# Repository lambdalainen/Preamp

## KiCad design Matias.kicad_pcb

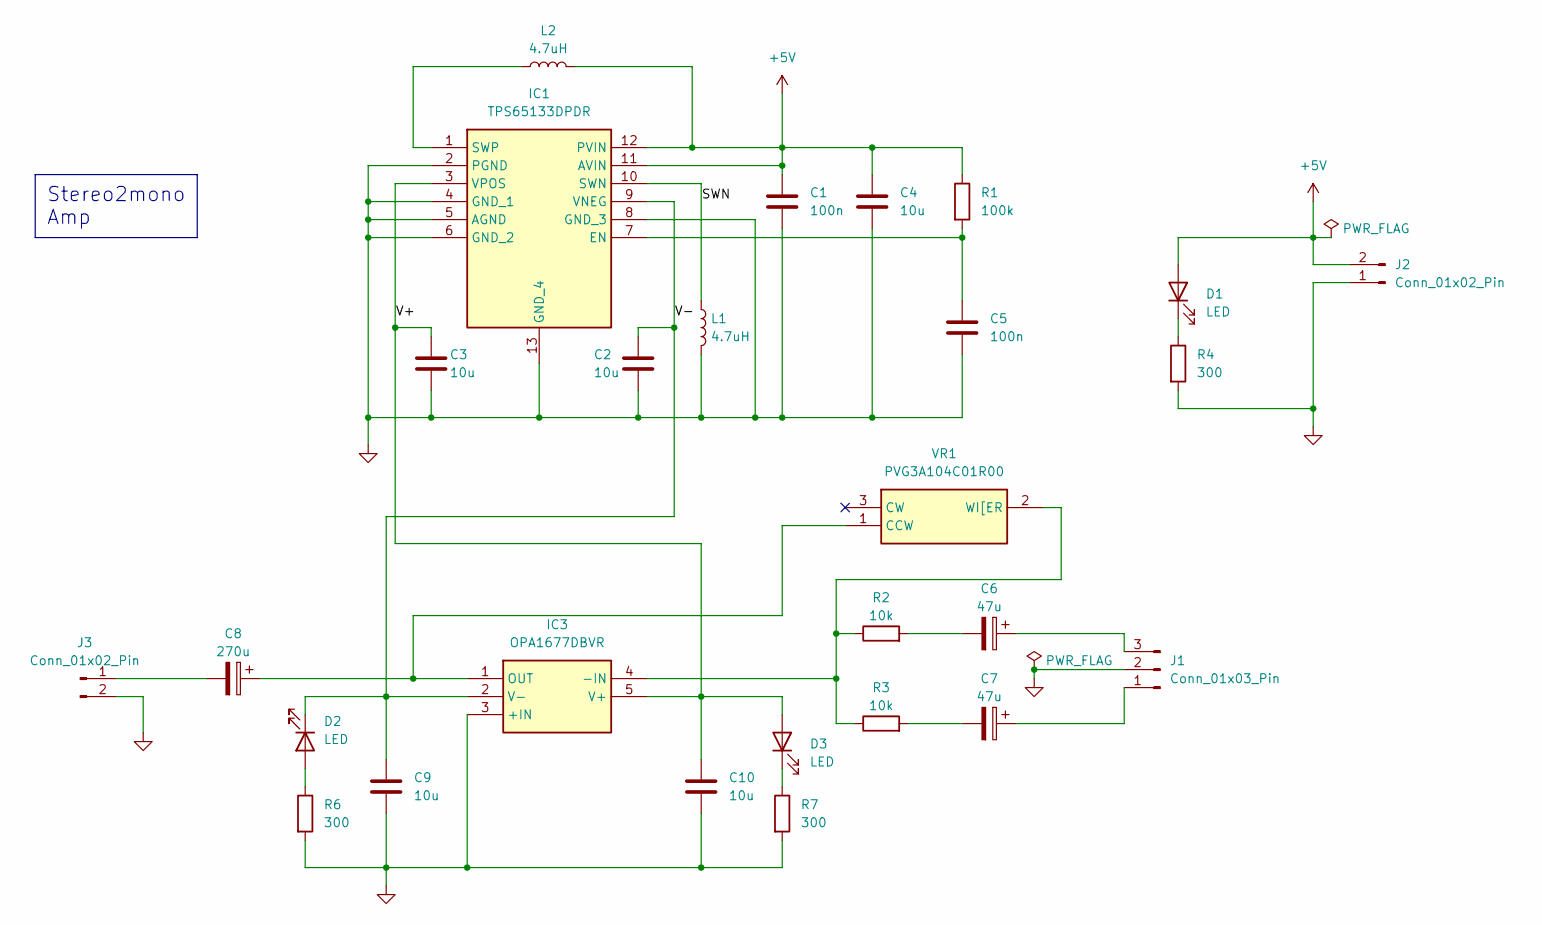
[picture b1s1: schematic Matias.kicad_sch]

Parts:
C1, C5: 100n; C_0603_1608Metric
C2, C3, C4: 10u; C_0805_2012Metric
C6, C7: 47u; CP_Radial_D5.0mm_P2.00mm
C8: 270u; CP_Radial_D6.3mm_P2.50mm
C9, C10: 10u; C_0603_1608Metric
D1, D2, D3: LED; LED_0603_1608Metric
IC1: TPS65133DPDR; SON45P300X300X80-13N-D; Manufacturer_Part_Number TPS65133DPDR; Mouser Part Number 595-TPS65133DPDR
IC3: OPA1677DBVR; SOT95P280X145-5N; Manufacturer_Part_Number OPA1677DBVR; Mouser Part Number 595-OPA1677DBVR
J1: Conn_01x03_Pin; PinHeader_1x03_P2.54mm_Vertical
J2, J3: Conn_01x02_Pin; PinHeader_1x02_P2.54mm_Vertical
L1, L2: 4.7uH; L_1008_2520Metric
R1: 100k; R_0603_1608Metric
R2, R3: 10k; R_0603_1608Metric
R4, R6, R7: 300; R_0603_1608Metric
VR1: PVG3A104C01R00; Manufacturer_Part_Number PVG3A104C01R00; Mouser Part Number 81-PVG3A104C01R00

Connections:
+5V: C1.1, C4.1, D1.2 (A), IC1.11 (AVIN), IC1.12 (PVIN), J2.2, L2.2, R1.1
/SWN: IC1.10 (SWN), L1.1
/V+: C3.1, C10.1, D3.2 (A), IC1.3 (VPOS), IC3.5 (V+)
/V-: C2.1, C9.1, D2.1 (K), IC1.9 (VNEG), IC3.2 (V-)
GND: C1.2, C2.2, C3.2, C4.2, C5.2, C9.2, C10.2, IC1.2 (PGND), IC1.4 (GND_1), IC1.5 (AGND), IC1.6 (GND_2), IC1.8 (GND_3), IC1.13 (GND_4), IC3.3 (+IN), J1.2, J2.1, J3.2, L1.2, R4.2, R6.2, R7.2
unnamed: C6.2, R2.2
unnamed: C7.2, R3.2
unnamed: D1.1 (K), R4.1
unnamed: D2.2 (A), R6.1
unnamed: D3.1 (K), R7.1
unnamed: C5.1, IC1.7 (EN), R1.2
unnamed: IC1.1 (SWP), L2.1
unnamed: IC3.4 (-IN), R2.1, R3.1, VR1.2 (WI[ER)
unnamed: C8.1, IC3.1 (OUT), VR1.1 (CCW)
unnamed: C7.1, J1.1
unnamed: C6.1, J1.3
unnamed: C8.2, J3.1

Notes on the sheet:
Stereo2mono Amp

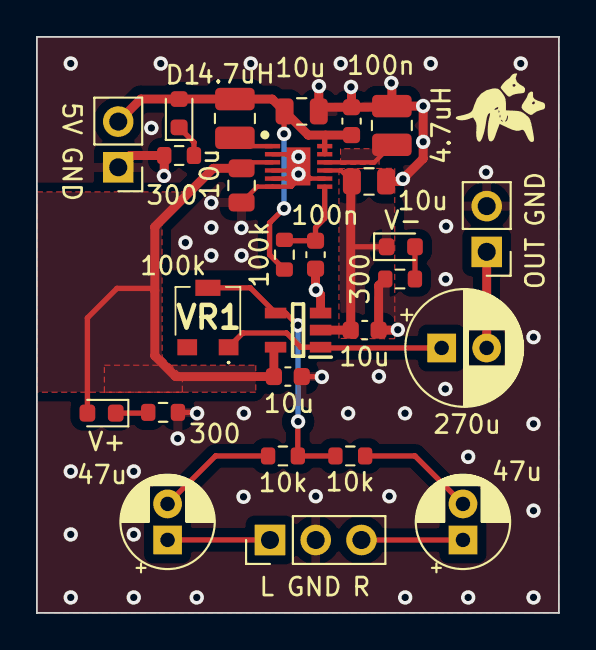
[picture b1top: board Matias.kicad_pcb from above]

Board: 2 copper layers, 29.0 x 32.0 mm, 27 parts (0 on the bottom side), 17 nets.

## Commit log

2024-02-11 Add TPS65133DPDR
    Split-Rail Converter, ±5V, 250mA Dual Output Power Supply
2024-02-12 Add OPA1677DBVR
    Low-distortion (-120 dB) low-noise (4.5 nV/rtHz) single audio operational amplifier
2024-02-12 Add 3362P-1-104LF
    100k trimmer
2024-02-17 Add PVG3A104C01R00
    Trimmer Resistors - SMD 100Kohms Sealed 3mm Sngl turn
    This is an alternative to 3362P-1-104LF with a smaller footprint
2024-02-17 Add custom design rules for JLCPCB, fp-lib-table and sym-lib-table
2024-02-17 Finish schematics and layout
2024-02-19 Plot Gerber files
2024-03-02 Typo
